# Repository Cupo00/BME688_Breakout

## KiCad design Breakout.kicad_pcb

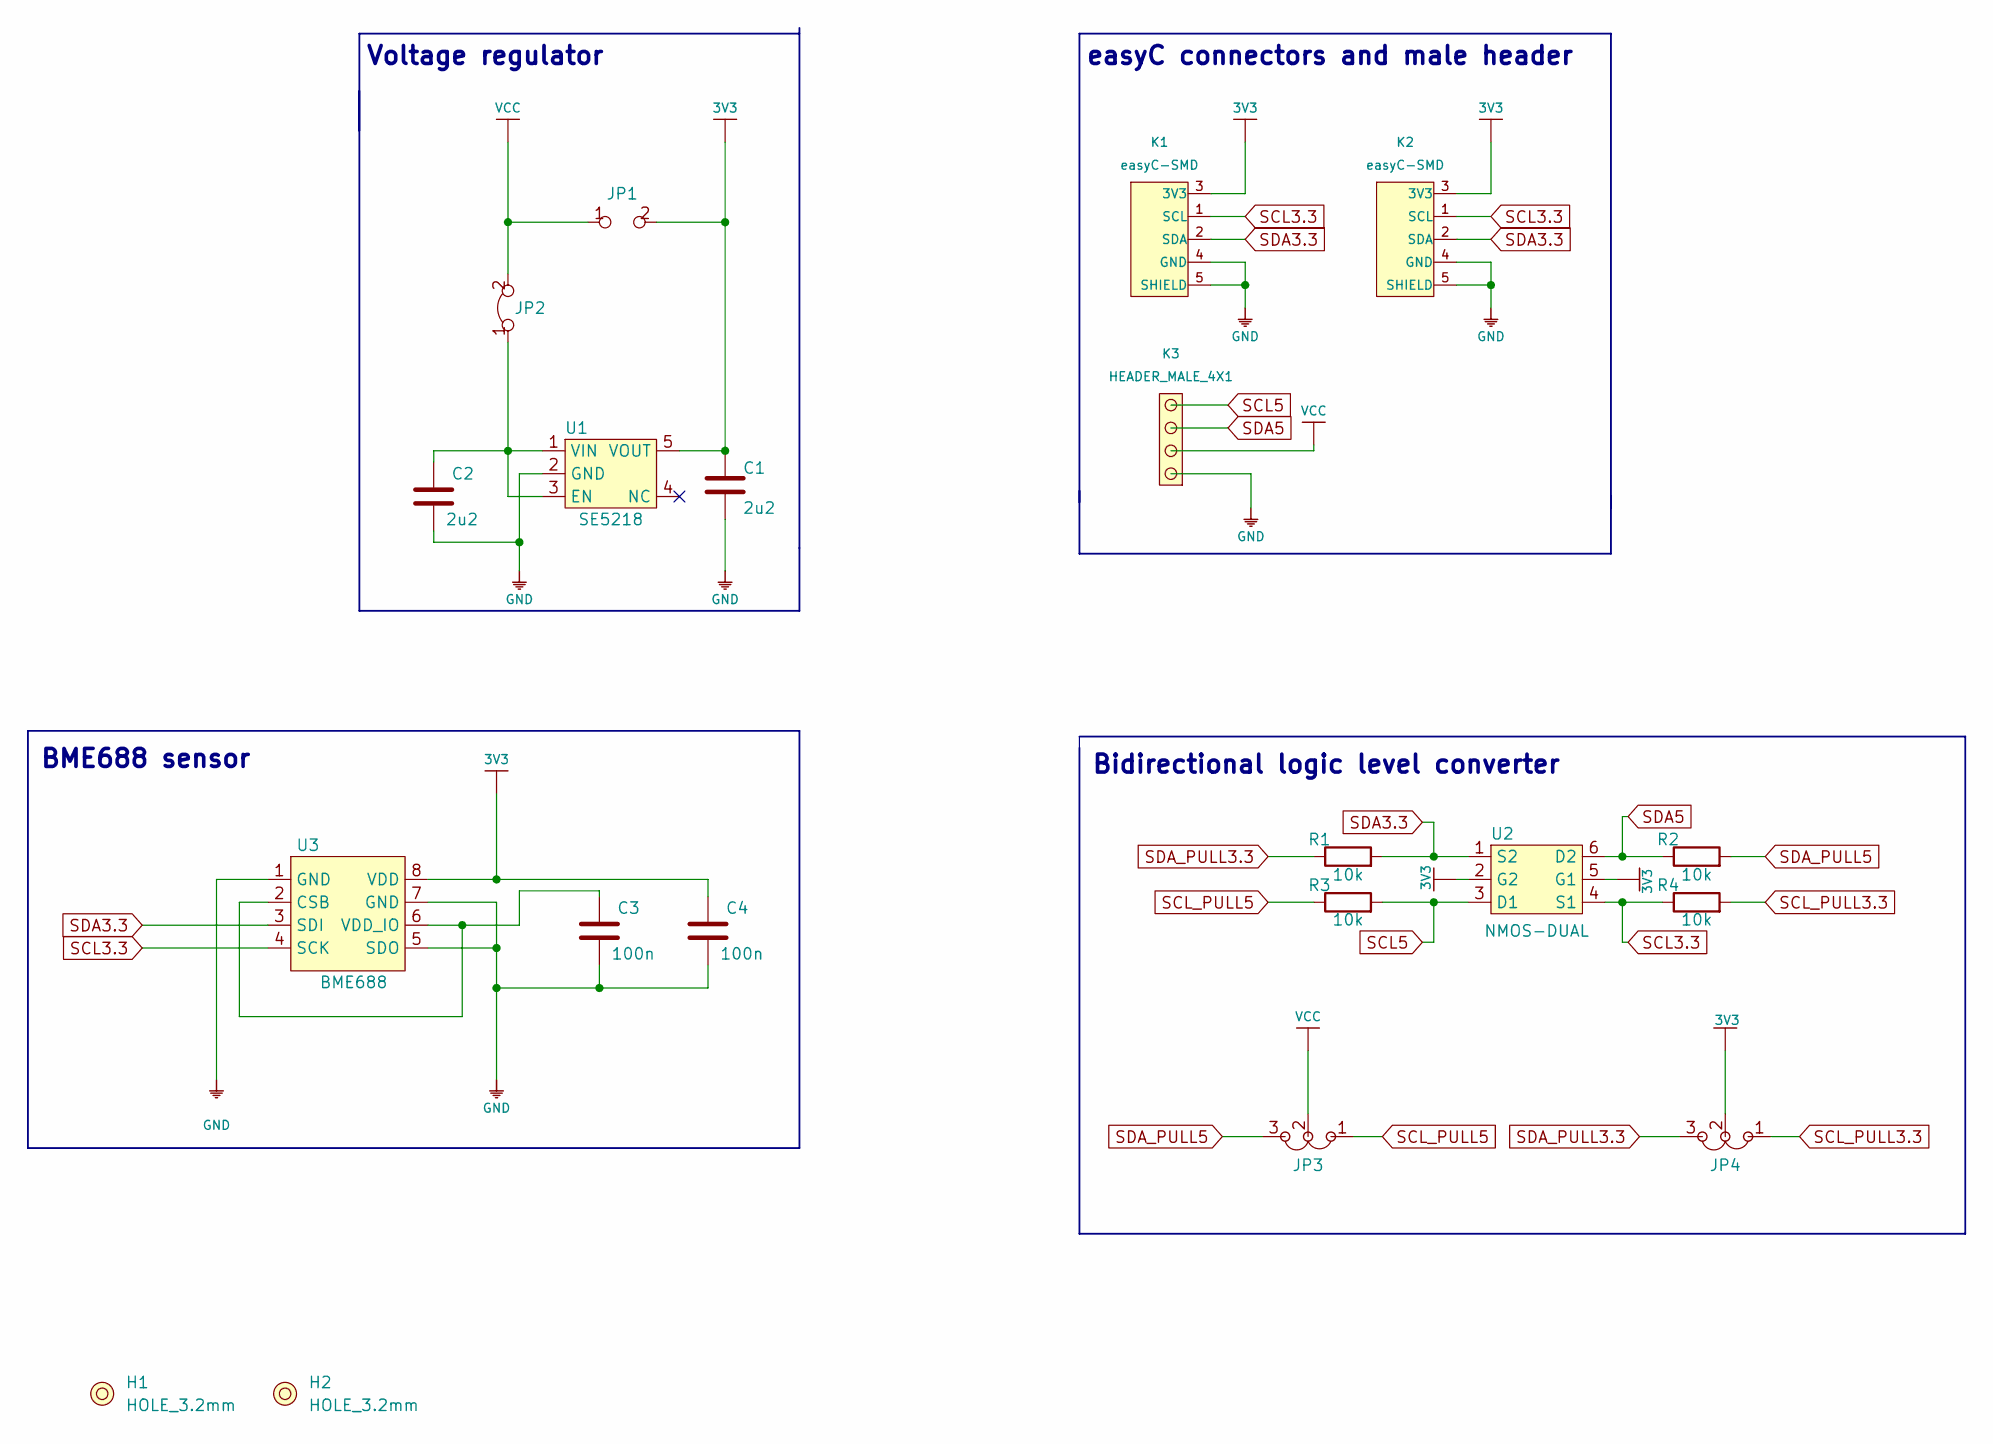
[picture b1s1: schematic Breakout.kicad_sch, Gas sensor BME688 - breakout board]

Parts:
C1, C2: 2u2; 0603C
C3, C4: 100n; 0603C
H1, H2: HOLE_3.2mm
JP1: SMD_JUMPER
JP2: SMD-JUMPER-CONNECTED_TRACE_SOLDERMASK
JP3, JP4: SMD_JUMPER_3_PAD_TRACE
K1, K2: easyC-SMD; easyC-connector
K3: HEADER_MALE_4X1
R1, R2, R3, R4: 10k; 0603R
U1: SE5218; SOT-23-5
U2: NMOS-DUAL; SOT-363
U3: BME688

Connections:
3V3: C1.1, C4.1, JP1.2, JP4.2, K1.3 (3V3), K2.3 (3V3), U1.5 (VOUT), U2.2 (G2), U2.5 (G1), U3.8 (VDD)
GND: C1.2, C2.2, C3.2, C4.2, K1.4 (GND), K1.5 (SHIELD), K2.4 (GND), K2.5 (SHIELD), K3.1, U1.2 (GND), U3.1 (GND), U3.5 (SDO), U3.7 (GND)
unnamed: C2.1, JP2.1, U1.1 (VIN), U1.3 (EN)
unnamed: C3.1, U3.2 (CSB), U3.6 (VDD_IO)
SCL3.3: K1.1 (SCL), K2.1 (SCL), R4.1, U2.4 (S1), U3.4 (SCK)
SCL5: K3.4, R3.2, U2.3 (D1)
SCL_PULL3.3: JP4.1, R4.2
SCL_PULL5: JP3.1, R3.1
SDA3.3: K1.2 (SDA), K2.2 (SDA), R1.2, U2.1 (S2), U3.3 (SDI)
SDA5: K3.3, R2.1, U2.6 (D2)
SDA_PULL3.3: JP4.3, R1.1
SDA_PULL5: JP3.3, R2.2
VCC: JP1.1, JP2.2, JP3.2, K3.2

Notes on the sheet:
easyC connectors and male header
Bidirectional logic level converter
Voltage regulator
BME688 sensor

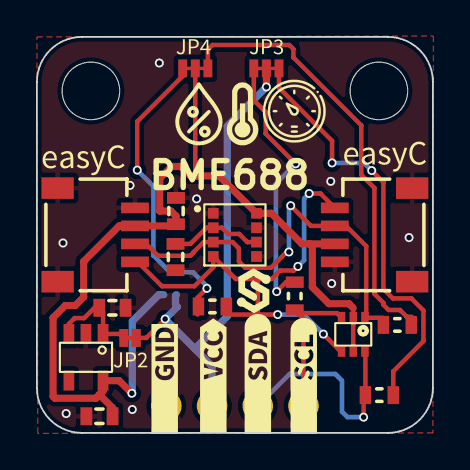
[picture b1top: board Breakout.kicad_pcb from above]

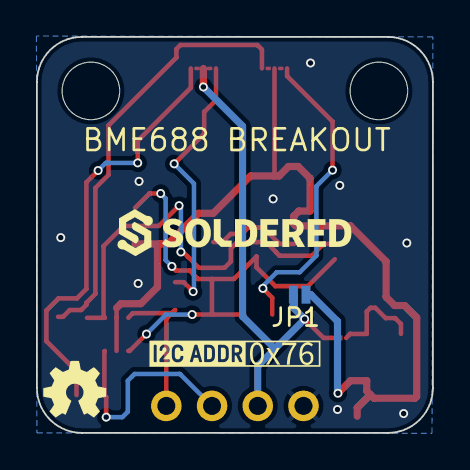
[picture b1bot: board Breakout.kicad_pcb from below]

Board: 2 copper layers, 22.0 x 22.0 mm, 28 parts (2 on the bottom side), 13 nets.

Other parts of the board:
kibuzzard-640F3A70: G***; kibuzzard-640F3A70
kibuzzard-640F3B06: G***; kibuzzard-640F3B06
kibuzzard-640F3C4D: G***; kibuzzard-640F3C4D
kibuzzard-640F3DD8: G***; kibuzzard-640F3DD8
kibuzzard-640F61A2: G***; kibuzzard-640F61A2
kibuzzard-640F698B: G***; kibuzzard-640F698B
kibuzzard-640F759F: G***; kibuzzard-640F759F
kibuzzard-640F6240: G***; kibuzzard-640F6240
